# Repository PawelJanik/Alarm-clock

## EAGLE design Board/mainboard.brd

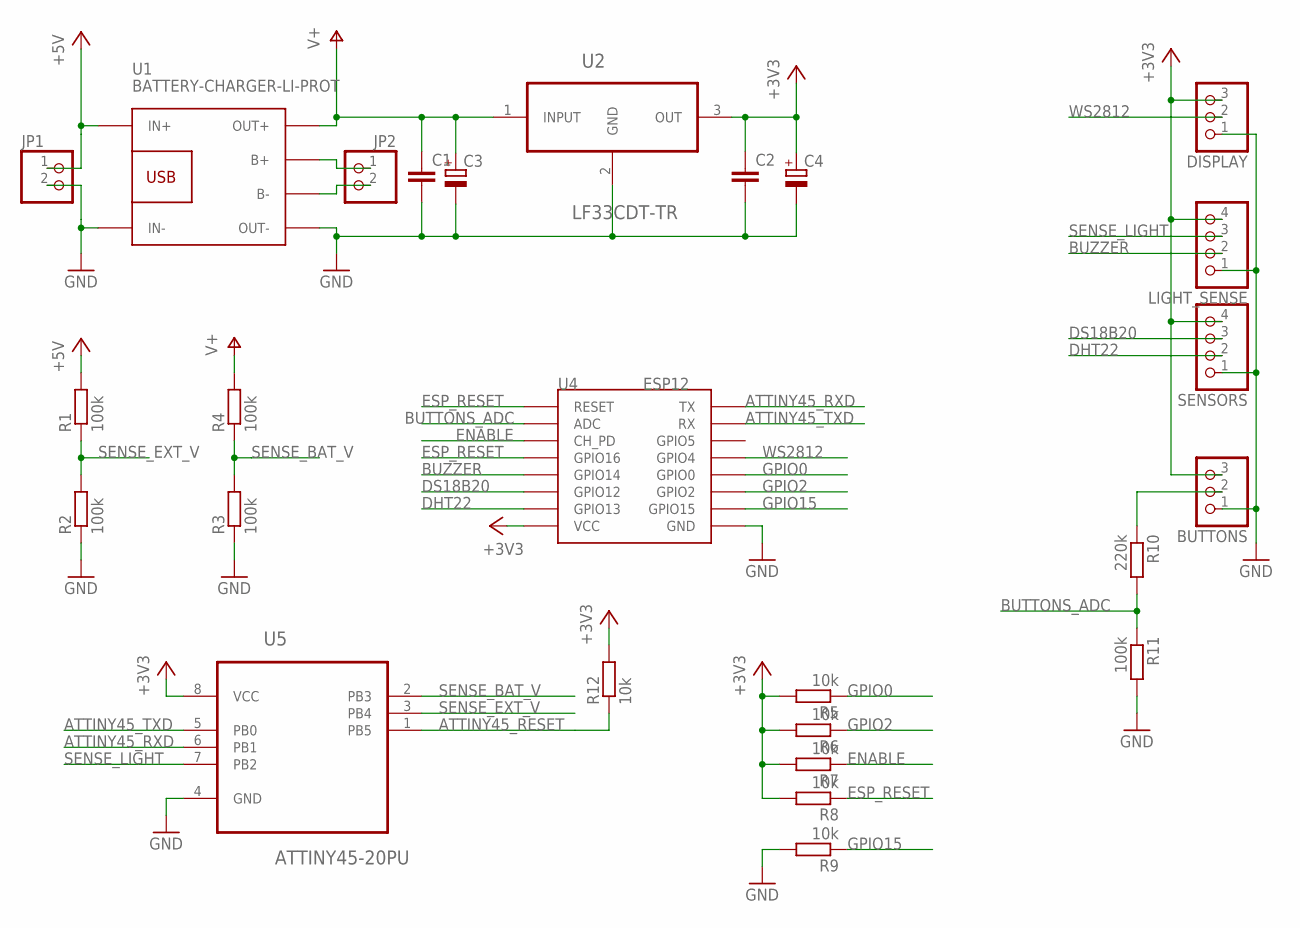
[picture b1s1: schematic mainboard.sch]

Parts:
BUTTONS: PINHD-1X3; 1X03
C1, C2: C-EUC1206; C1206
C3, C4: CPOL-EUE2-5; E2-5
DISPLAY: PINHD-1X3; 1X03
JP1, JP2: PINHD-1X2; 1X02
LIGHT_SENSE: PINHD-1X4; 1X04
R1, R2, R3, R4, R11: 100k; R1206
R5, R6, R7, R8, R9, R12: 10k; R1206
R10: 220k; R1206
SENSORS: PINHD-1X4; 1X04
U1: BATTERY-CHARGER-LI-PROT
U2: LF33CDT-TR; TO228P972X240-3N
U4: ESP12
U5: ATTINY45-20PU; DIP254P762X533-8

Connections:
+3V3: BUTTONS.3, C2.1, C4.+, DISPLAY.3, LIGHT_SENSE.4, R5.2, R6.2, R7.2, R8.2, R12.2, SENSORS.4, U2.3 (OUT), U4.VCC, U5.8 (VCC)
+5V: JP1.1, R1.2, U1.IN+
ATTINY45_RESET: R12.1, U5.1 (PB5)
ATTINY45_RXD: U4.TX, U5.6 (PB1)
ATTINY45_TXD: U4.RX, U5.5 (PB0)
BUTTONS_ADC: R10.2, R11.1, U4.ADC
BUZZER: LIGHT_SENSE.2, U4.GPIO14
DHT22: SENSORS.2, U4.GPIO13
DS18B20: SENSORS.3, U4.GPIO12
ENABLE: R7.1, U4.CH_PD
ESP_RESET: R8.1, U4.GPIO16, U4.RESET
GND: BUTTONS.1, C1.2, C2.2, C3.-, C4.-, DISPLAY.1, JP1.2, LIGHT_SENSE.1, R2.1, R3.1, R9.2, R11.2, SENSORS.1, U1.IN-, U1.OUT-, U2.2 (GND), U4.GND, U5.4 (GND)
GPIO0: R5.1, U4.GPIO0
GPIO2: R6.1, U4.GPIO2
GPIO15: R9.1, U4.GPIO15
unnamed: BUTTONS.2, R10.1
unnamed: JP2.1, U1.B+
unnamed: JP2.2, U1.B-
SENSE_BAT_V: R3.2, R4.1, U5.2 (PB3)
SENSE_EXT_V: R1.1, R2.2, U5.3 (PB4)
SENSE_LIGHT: LIGHT_SENSE.3, U5.7 (PB2)
V+: C1.1, C3.+, R4.2, U1.OUT+, U2.1 (INPUT)
WS2812: DISPLAY.2, U4.GPIO5 (GPIO4)

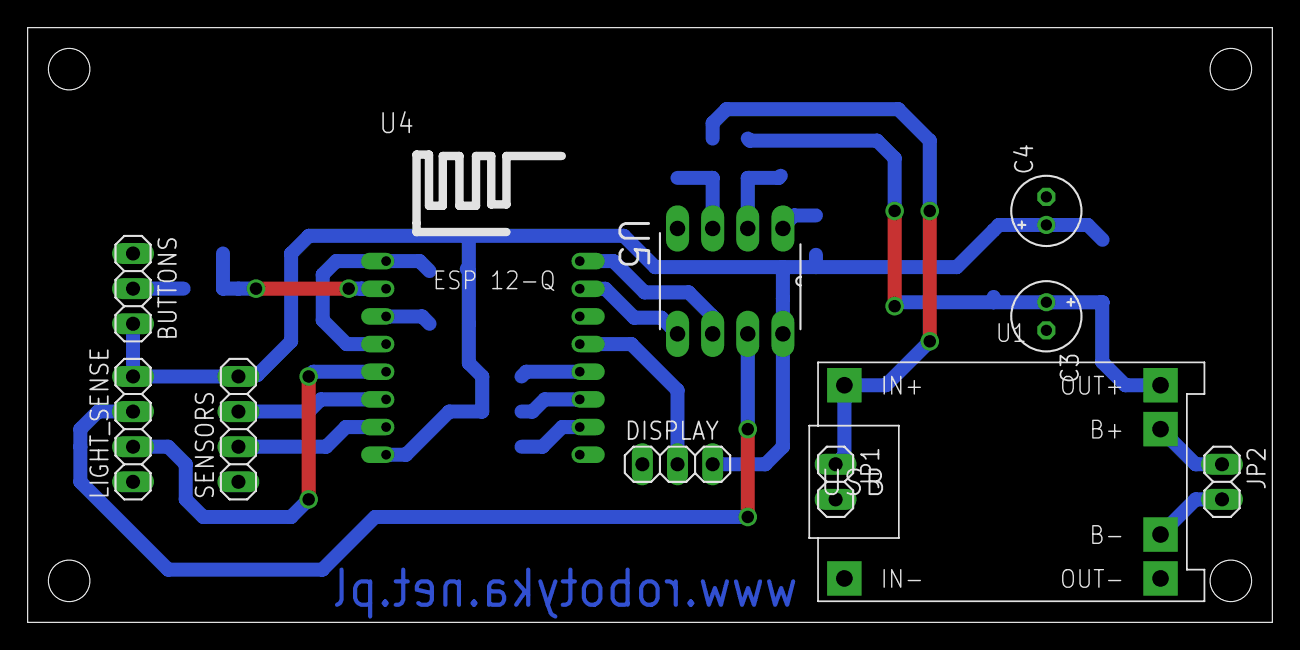
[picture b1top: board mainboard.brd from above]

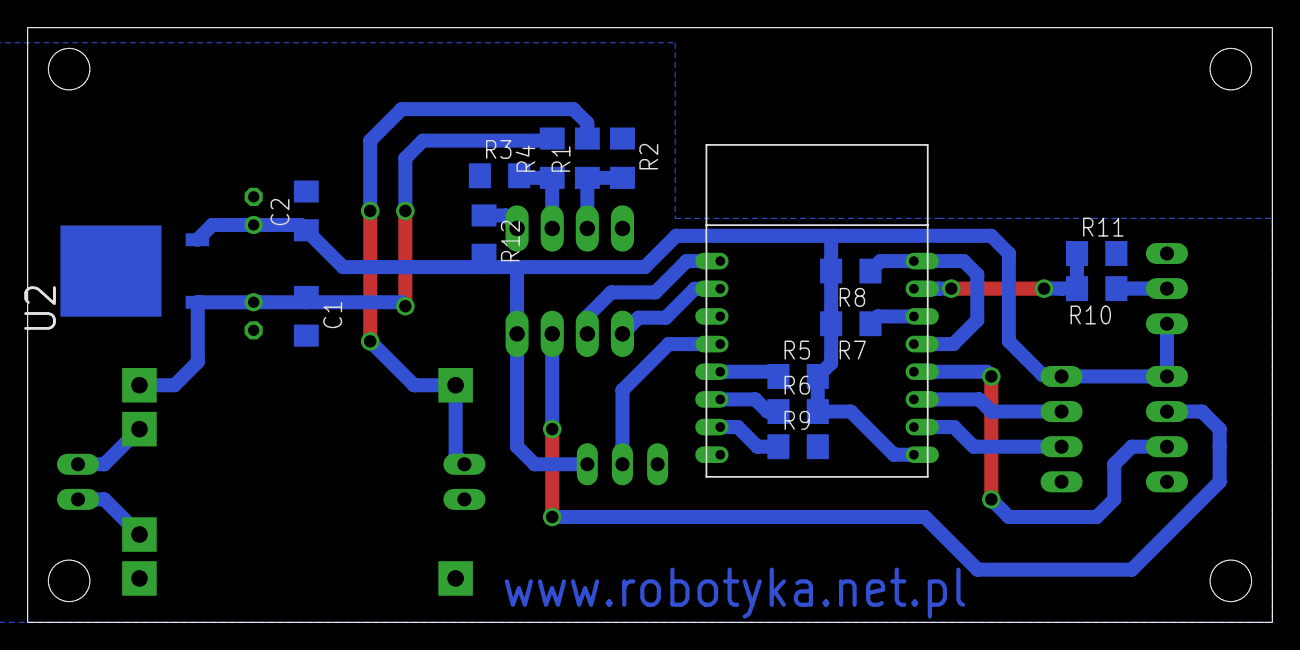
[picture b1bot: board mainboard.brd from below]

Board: 2 copper layers, 90.0 x 43.0 mm, 26 parts (15 on the bottom side), 23 nets.

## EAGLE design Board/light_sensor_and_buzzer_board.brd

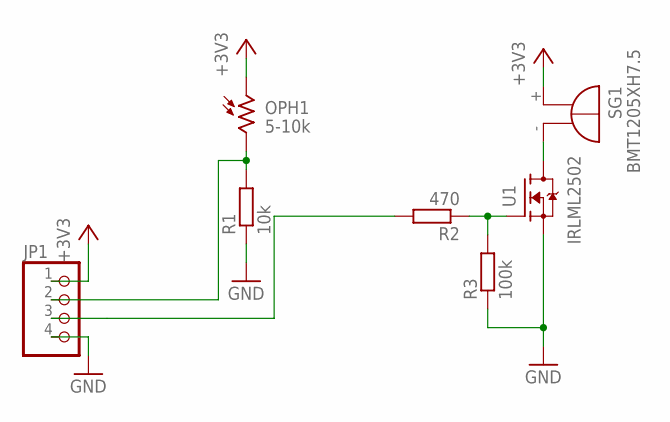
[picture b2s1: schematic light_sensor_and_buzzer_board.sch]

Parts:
JP1: PINHD-1X4; 1X04
OPH1: 5-10k; VT900
R1: 10k; R1206
R2: 470; R1206
R3: 100k; R1206
SG1: BMT1205XH7.5
U1: IRLML2502; SOT23

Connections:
+3V3: JP1.1, OPH1.1, SG1.+
GND: JP1.4, R1.1, R3.1, U1.2 (S)
unnamed: JP1.2, OPH1.2, R1.2
unnamed: SG1.-, U1.3 (D)
unnamed: R2.1, R3.2, U1.1 (G)
unnamed: JP1.3, R2.2

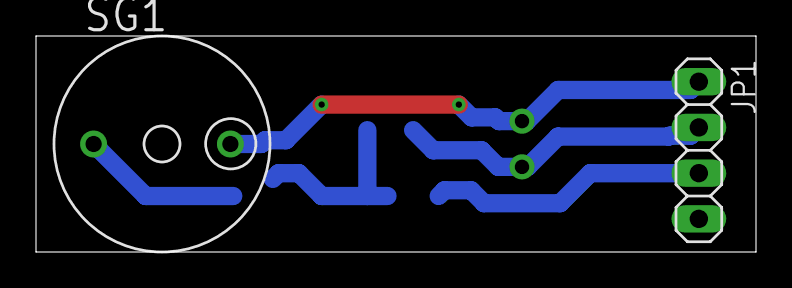
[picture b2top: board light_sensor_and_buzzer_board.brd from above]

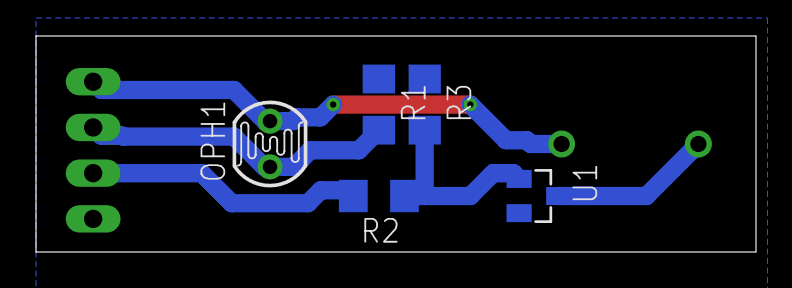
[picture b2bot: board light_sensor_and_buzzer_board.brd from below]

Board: 2 copper layers, 40.0 x 12.0 mm, 7 parts (5 on the bottom side), 6 nets.

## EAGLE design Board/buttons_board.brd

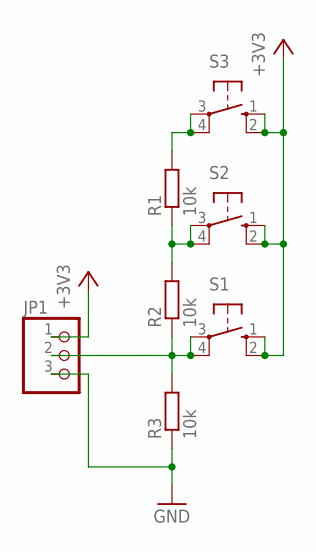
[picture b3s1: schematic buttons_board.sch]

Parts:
JP1: PINHD-1X3/90; 1X03/90
R1, R2, R3: 10k; R1206
S1, S2, S3: 10-XX; B3F-10XX

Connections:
+3V3: JP1.1, S1.1 (S), S1.2 (S1), S2.1 (S), S2.2 (S1), S3.1 (S), S3.2 (S1)
GND: JP1.3, R3.1
unnamed: JP1.2, R2.1, R3.2, S1.3, S1.4 (P1)
unnamed: R1.1, R2.2, S2.3, S2.4 (P1)
unnamed: R1.2, S3.3, S3.4 (P1)

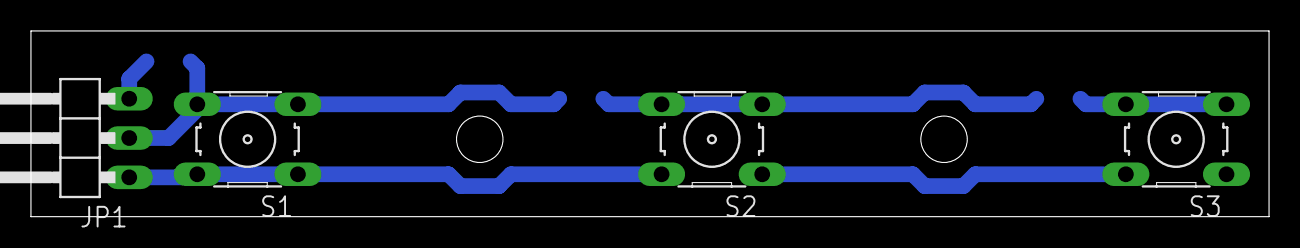
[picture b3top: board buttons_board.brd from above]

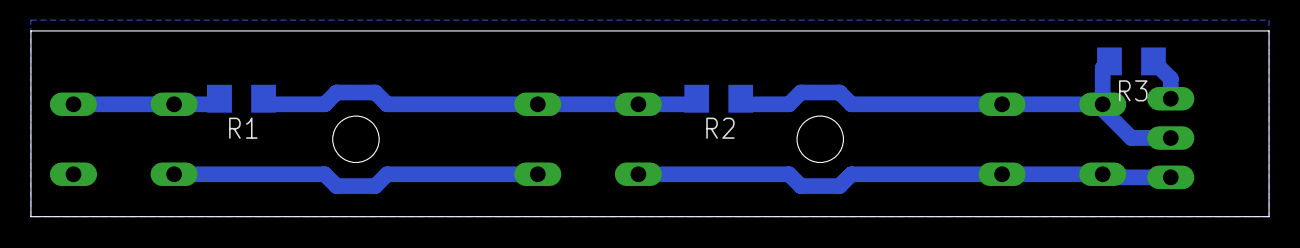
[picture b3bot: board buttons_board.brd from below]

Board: 2 copper layers, 80.0 x 12.0 mm, 7 parts (3 on the bottom side), 5 nets.

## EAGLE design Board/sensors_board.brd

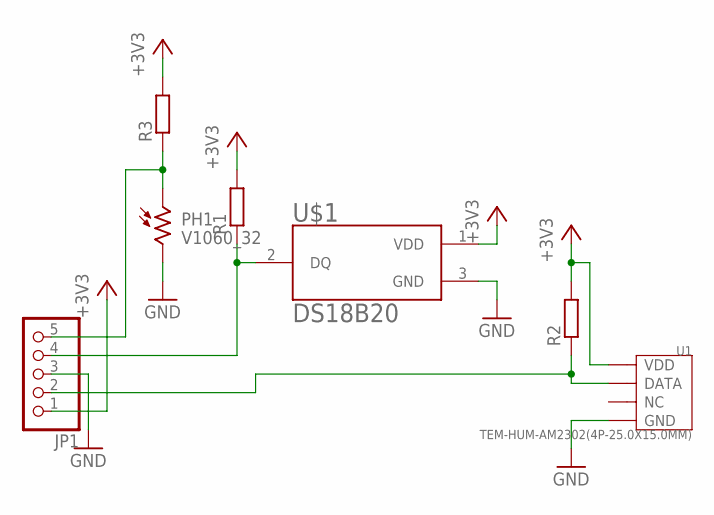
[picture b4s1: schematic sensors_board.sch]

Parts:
JP1: PINHD-1X5/90; 1X05/90
PH1: V1060_32; TO-5_V10
R1, R2, R3: R-EU_R1206; R1206
U1: TEM-HUM-AM2302(4P-25.0X15.0MM); SNR4-2.54-25.0X15.0X7.0MM
U$1: DS18B20; TO92-

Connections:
+3V3: JP1.1, R1.2, R2.2, R3.2, U1.P$1 (VDD), U$1.1 (VDD)
GND: JP1.3, PH1.2, U1.P$4 (GND), U$1.3 (GND)
unnamed: JP1.2, R2.1, U1.P$2 (DATA)
unnamed: JP1.4, R1.1, U$1.2 (DQ)
unnamed: JP1.5, PH1.1, R3.1

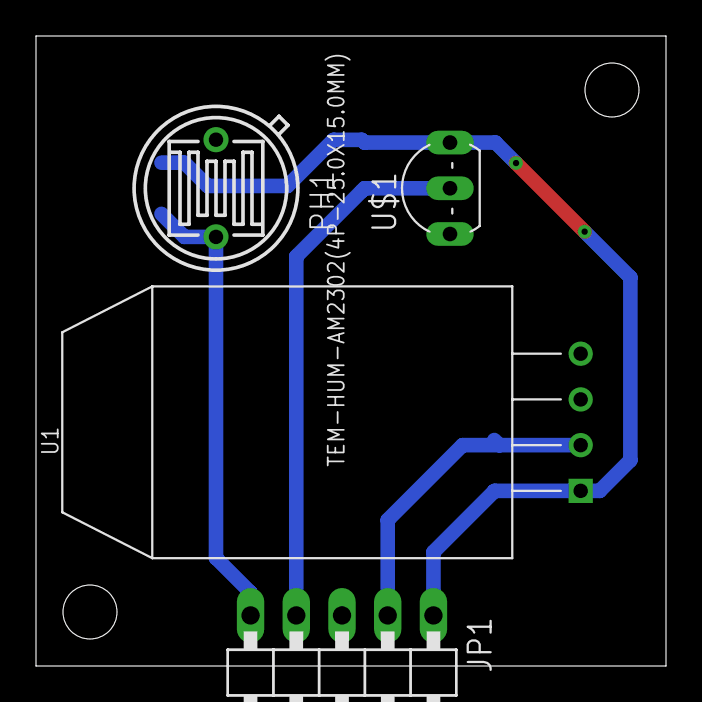
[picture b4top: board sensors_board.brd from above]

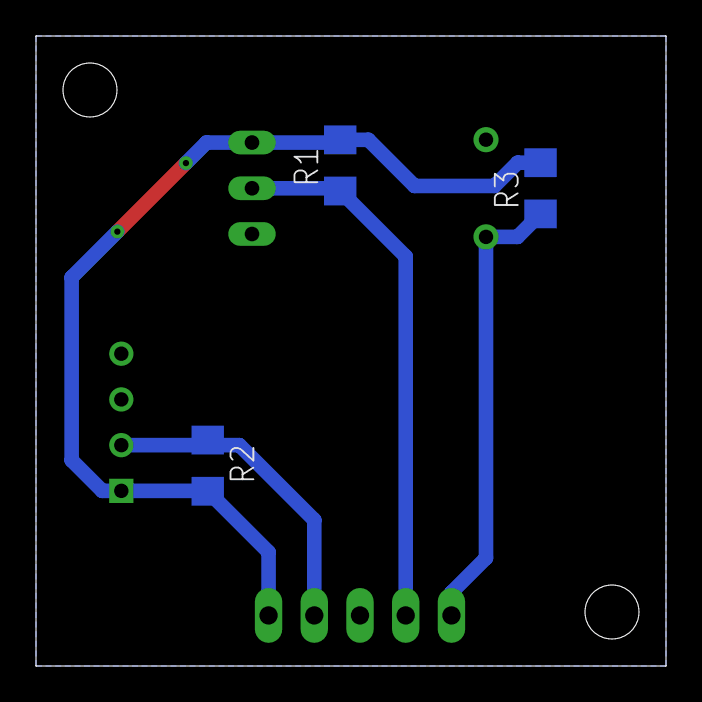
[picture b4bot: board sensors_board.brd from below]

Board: 2 copper layers, 35.0 x 35.0 mm, 7 parts (3 on the bottom side), 5 nets.

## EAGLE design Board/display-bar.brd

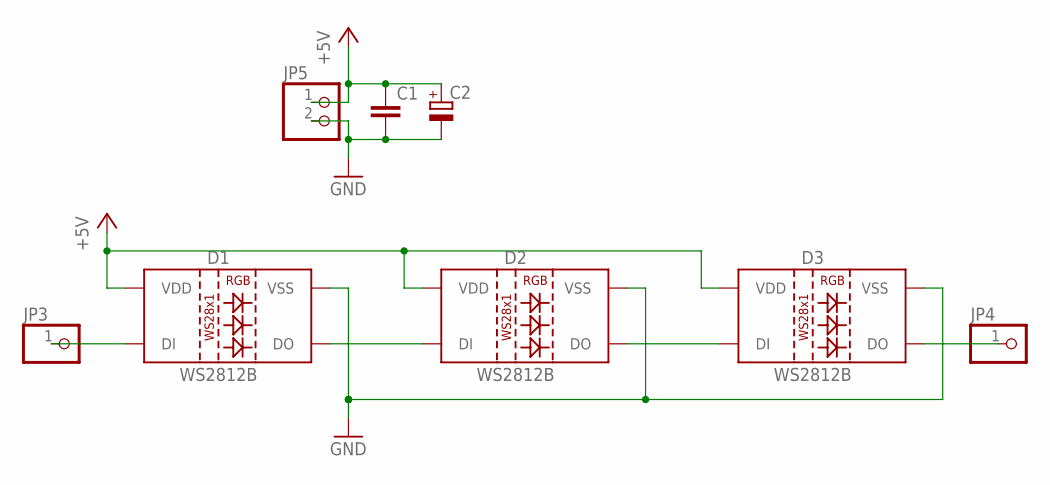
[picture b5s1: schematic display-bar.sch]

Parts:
C1: C-EUC1206; C1206
C2: CPOL-EUE2.5-6; E2,5-6
D1, D2, D3: WS2812B
JP3, JP4: PINHD-1X1; 1X01
JP5: PINHD-1X2; 1X02

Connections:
+5V: C1.1, C2.+, D1.1 (VDD), D2.1 (VDD), D3.1 (VDD), JP5.1
GND: C1.2, C2.-, D1.3 (VSS), D2.3 (VSS), D3.3 (VSS), JP5.2
unnamed: D3.2 (DO), JP4.1
unnamed: D2.2 (DO), D3.4 (DI)
unnamed: D1.2 (DO), D2.4 (DI)
unnamed: D1.4 (DI), JP3.1

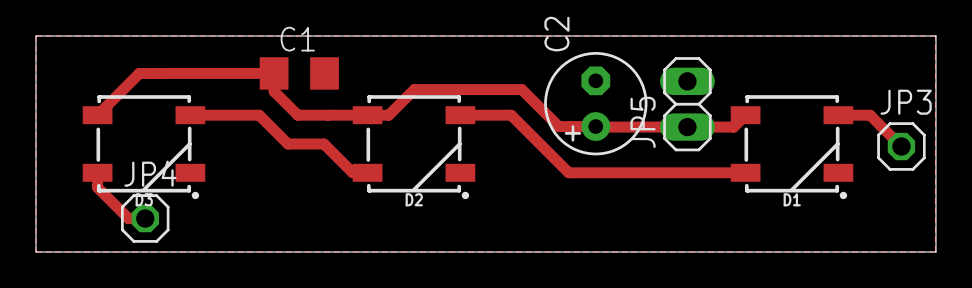
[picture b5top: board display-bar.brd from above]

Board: 2 copper layers, 50.0 x 12.0 mm, 8 parts (0 on the bottom side), 6 nets.

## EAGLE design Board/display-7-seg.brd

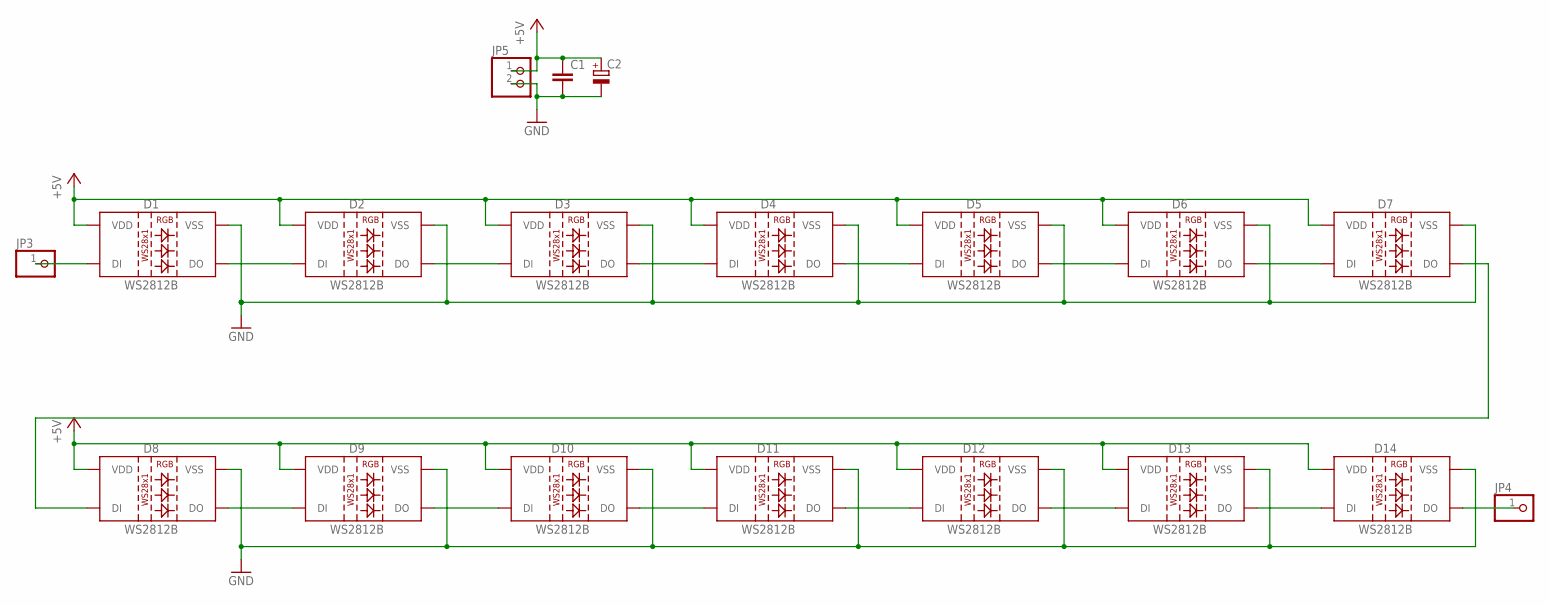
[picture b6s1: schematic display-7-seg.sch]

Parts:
C1: C-EUC1206; C1206
C2: CPOL-EUE2.5-6; E2,5-6
D1, D2, D3, D4, D5, D6, D7, D8, D9, D10, D11, D12, D13, D14: WS2812B
JP3, JP4: PINHD-1X1; 1X01
JP5: PINHD-1X2; 1X02

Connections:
+5V: C1.1, C2.+, D1.1 (VDD), D2.1 (VDD), D3.1 (VDD), D4.1 (VDD), D5.1 (VDD), D6.1 (VDD), D7.1 (VDD), D8.1 (VDD), D9.1 (VDD), D10.1 (VDD), D11.1 (VDD), D12.1 (VDD), D13.1 (VDD), D14.1 (VDD), JP5.1
GND: C1.2, C2.-, D1.3 (VSS), D2.3 (VSS), D3.3 (VSS), D4.3 (VSS), D5.3 (VSS), D6.3 (VSS), D7.3 (VSS), D8.3 (VSS), D9.3 (VSS), D10.3 (VSS), D11.3 (VSS), D12.3 (VSS), D13.3 (VSS), D14.3 (VSS), JP5.2
unnamed: D7.2 (DO), D8.4 (DI)
unnamed: D14.2 (DO), JP4.1
unnamed: D1.2 (DO), D2.4 (DI)
unnamed: D2.2 (DO), D3.4 (DI)
unnamed: D3.2 (DO), D4.4 (DI)
unnamed: D4.2 (DO), D5.4 (DI)
unnamed: D5.2 (DO), D6.4 (DI)
unnamed: D6.2 (DO), D7.4 (DI)
unnamed: D8.2 (DO), D9.4 (DI)
unnamed: D9.2 (DO), D10.4 (DI)
unnamed: D10.2 (DO), D11.4 (DI)
unnamed: D11.2 (DO), D12.4 (DI)
unnamed: D12.2 (DO), D13.4 (DI)
unnamed: D13.2 (DO), D14.4 (DI)
unnamed: D1.4 (DI), JP3.1

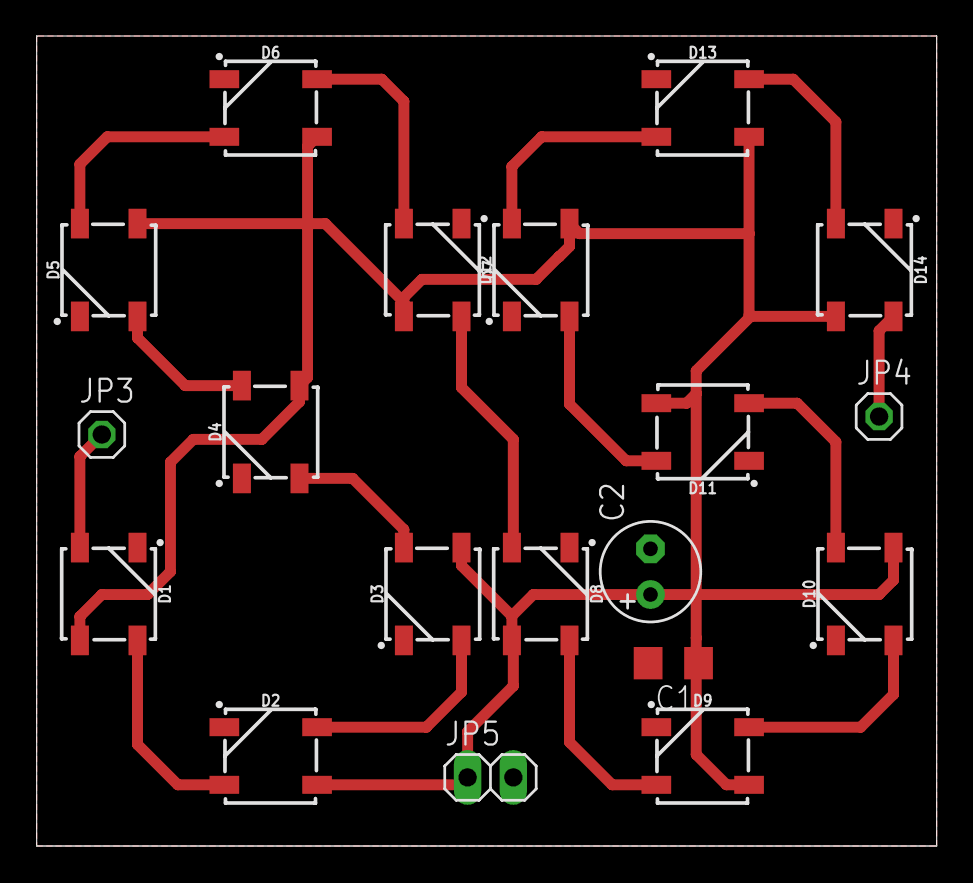
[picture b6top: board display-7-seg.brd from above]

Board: 2 copper layers, 50.0 x 45.0 mm, 19 parts (0 on the bottom side), 17 nets.

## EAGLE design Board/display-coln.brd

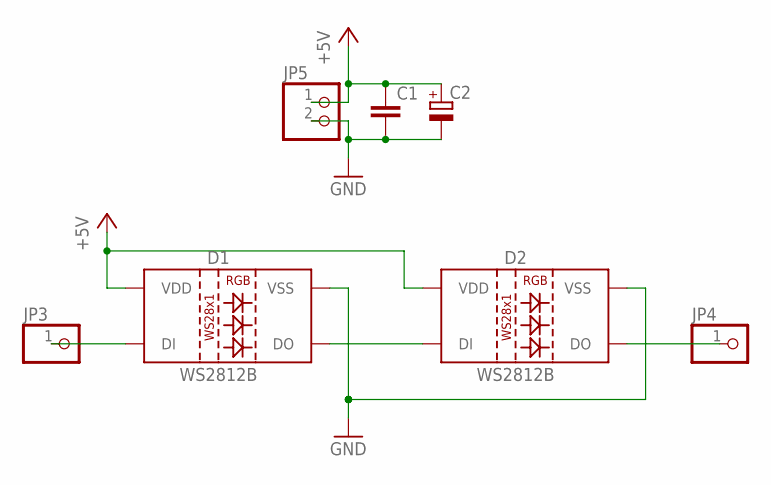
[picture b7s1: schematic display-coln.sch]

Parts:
C1: C-EUC1206; C1206
C2: CPOL-EUE2.5-6; E2,5-6
D1, D2: WS2812B
JP3, JP4: PINHD-1X1; 1X01
JP5: PINHD-1X2; 1X02

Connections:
+5V: C1.1, C2.+, D1.1 (VDD), D2.1 (VDD), JP5.1
GND: C1.2, C2.-, D1.3 (VSS), D2.3 (VSS), JP5.2
unnamed: D2.2 (DO), JP4.1
unnamed: D1.2 (DO), D2.4 (DI)
unnamed: D1.4 (DI), JP3.1

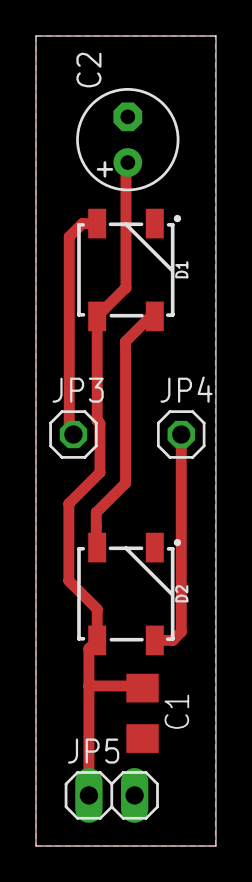
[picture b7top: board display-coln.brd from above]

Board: 2 copper layers, 10.0 x 45.0 mm, 7 parts (0 on the bottom side), 5 nets.

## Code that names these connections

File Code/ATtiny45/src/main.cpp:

#include <Arduino.h>
#include <avr/sleep.h>
#include "prescaler.h"

#define SENSE_EXT_V_PIN A2
#define SENSE_BAT_V_PIN A3
#define SENSE_LIGHT_PIN A1

#define ANALOG_RATIO 3.22	//----for 3.3V
//#define ANALOG_RATIO 4.88	//----for 5V

unsigned long timer200ms = 0;
unsigned long timer5s = 0;
unsigned long timer1m = 0;

int16_t lastLightValue = 0;
unsigned long lightTimer = 0;

void setup()
{
	setClockPrescaler(CLOCK_PRESCALER_8);	//-----------------------------------------------------------
	pinMode(3, OUTPUT);

	pinMode(SENSE_EXT_V_PIN, INPUT);
	pinMode(SENSE_BAT_V_PIN, INPUT);

	Serial.begin(9600);
}

void loop()
{
	if((millis() - timer200ms) > 200)
	{
		timer200ms = millis();

		int16_t lightValue = analogRead(SENSE_LIGHT_PIN);
		if(((lightValue - 10) > lastLightValue) || ((lightValue + 10) < lastLightValue))
		{
			Serial.print("-LIG:");
			Serial.println(lightValue);
			lastLightValue = lightValue;
		}
		else if((millis() - lightTimer) > 1000)
		{
			lightTimer = millis();

			Serial.print("-LIG:");
			Serial.println(lightValue);
			lastLightValue = lightValue;
		}
	}

	if((millis() - timer5s) > 1000*5)	//----------------------------to changed
	{
		timer5s = millis();

		Serial.print("-EXT:");
		Serial.println(analogRead(SENSE_EXT_V_PIN)*(double)ANALOG_RATIO/500);
	}

	if((millis() - timer1m) > 10000*60)
	{
		timer1m = millis();

		Serial.print("-BAT:");
		Serial.println(analogRead(SENSE_BAT_V_PIN)*(double)ANALOG_RATIO/500);
	}
}

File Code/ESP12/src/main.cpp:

#include "config.h"
#include "main.h"

#include <PubSubClient.h>
#include <ESP8266WiFi.h>
#include <ESP8266mDNS.h>
#include <WiFiUdp.h>
#include <ArduinoOTA.h>
#include <EEPROM.h>

#include <Adafruit_NeoPixel.h>

#include <TimeLib.h>
#include <NTPClient.h>

#include <Adafruit_Sensor.h>
#include <DHT.h>

#include <OneWire.h>
#include <DallasTemperature.h>

#include "setup.h"
#include "display.h"

#define WS2812_PIN 4
#define DHT_PIN 13
#define DS18B20_PIN 12
#define BUZZER_PIN 14
#define BUTTONS_PIN A0

#define DHTTYPE DHT22     // DHT 22 (AM2302)
#define pixelCount 33

unsigned long timer10ms = 0;
unsigned long timer1s = 0;
unsigned long timer10s = 0;
unsigned long timer1m = 0;

WiFiClient espClient;
PubSubClient client(espClient);

WiFiUDP ntpUDP;
NTPClient timeClient(ntpUDP, "europe.pool.ntp.org");

Adafruit_NeoPixel strip = Adafruit_NeoPixel(pixelCount, WS2812_PIN, NEO_GRB + NEO_KHZ800);
Display * display;

DHT dht(DHT_PIN, DHTTYPE);

OneWire oneWire(DS18B20_PIN);
DallasTemperature ds18b20(&oneWire);

ButtonState buttonsState[3];

time_t requestSync()
{
	timeClient.update();
	time_t timestamp = timeClient.getEpochTime();
	setTime(timestamp);

	return 0;
}

void reconnect()
{
	digitalWrite(1, LOW);

	//if (client.connect(controllerName, mqttLogin, mqttPasswd))
	if (client.connect(controllerName))
	{
		client.subscribe("home/controllers/3/restart");
		client.subscribe("home/controllers/3/sleep");

		client.subscribe("home/myRoom/alarmClock/dateTime/timestamp");
		client.subscribe("home/myRoom/alarmClock/dateTime/timeZone");
		client.subscribe("home/myRoom/alarmClock/dateTime/DST");

		client.subscribe("home/myRoom/alarmClock/brightness");
		client.subscribe("home/myRoom/alarmClock/displayColor");
		client.subscribe("home/myRoom/alarmClock/displayState");

		client.subscribe("home/myRoom/alarmClock/tempInColor");
		client.subscribe("home/myRoom/alarmClock/tempOutColor");

		client.subscribe("home/myRoom/alarmClock/buzzerState");

		digitalWrite(1, HIGH);
	}
}

void callback(char * topic, byte* payload, unsigned int length)
{
	if(strcmp(topic,"home/controllers/3/restart")==0)
	{
		if((char)payload[0] == 'r')
		{
			client.publish("home/controllers/3/condition", "reset");
			delay(500);

			ESP.restart();
		}
	}

	if(strcmp(topic,"home/controllers/3/sleep")==0)
	{
		if((char)payload[0] == 's')
		{
			client.publish("home/controllers/3/condition", "sleep");
			delay(500);

			ESP.deepSleep(5 * 1000000, WAKE_RF_DEFAULT);
			//-----------------------------------------------------------------------------------------
			delay(10);
		}
	}

	if(strcmp(topic,"home/myRoom/alarmClock/dateTime/timestamp")==0)
	{
		time_t timestamp = bytesToInt(payload,length);

		setTime(timestamp);
	}

	if(strcmp(topic,"home/myRoom/alarmClock/dateTime/timeZone")==0)
	{
		int8_t timeZone = bytesToInt(payload,length);

		timeClient.setTimeOffset((timeZone * 3600) + (EEPROM.read(EEPROM_DST) * 3600));
		requestSync();

		EEPROM.write(EEPROM_TIME_ZONE, timeZone);
		EEPROM.commit();
	}

	if(strcmp(topic,"home/myRoom/alarmClock/dateTime/DST")==0)
	{
		int8_t DST = bytesToInt(payload,length);

		if((DST == 0) || (DST == 1))
		{
			timeClient.setTimeOffset((EEPROM.read(EEPROM_TIME_ZONE) * 3600) + (DST * 3600));
			requestSync();

			EEPROM.write(EEPROM_DST, DST);
			EEPROM.commit();
		}
	}

	if(strcmp(topic,"home/myRoom/alarmClock/brightness")==0)
	{
		int value = bytesToInt(payload,length);

		display->setBrightness(value);
	}

	if(strcmp(topic,"home/myRoom/alarmClock/displayColor")==0)
	{
		uint32_t color = bytesToUint32(payload,length);
		display->setColor(color);
	}

	if(strcmp(topic,"home/myRoom/alarmClock/displayState")==0)
	{
		char state = payload[0];

		if(state == '0')
		{
			display->displayOff(false,true,false,false);
		}
		else if(state == '1')
		{
			display->displayOn();
		}
	}

	if(strcmp(topic,"home/myRoom/alarmClock/tempInColor")==0)
	{
		uint32_t color = bytesToUint32(payload,length);
		display->setTempInColor(color);
	}

	if(strcmp(topic,"home/myRoom/alarmClock/tempOutColor")==0)
	{
		uint32_t color = bytesToUint32(payload,length);
		display->setTempOutColor(color);
	}

	if(strcmp(topic,"home/myRoom/alarmClock/buzzerState")==0)
	{
		char state = payload[0];

		if(state == '0')
		{
			digitalWrite(BUZZER_PIN, LOW);
		}
		else if(state == '1')
		{
			digitalWrite(BUZZER_PIN, HIGH);
		}
	}
}

void setup()
{
	Serial.begin(9600);

	EEPROM.begin(256);

	WIFIsetup();
	OTAsetup();
	client.setServer(mqttIP, mqttPort);
	client.setCallback(callback);
	reconnect();

	timeClient.setTimeOffset((EEPROM.read(EEPROM_TIME_ZONE) * 3600) + (EEPROM.read(EEPROM_DST) * 3600));
	timeClient.begin();
	setSyncProvider(requestSync);
	setSyncInterval(60);	//------------------------------------------------------to changed on 60*60*24

	display = new Display(&strip);

	display->setColor(234534534);
	display->setAnimatedColon(true);

	dht.begin();
	ds18b20.begin();

	pinMode(BUZZER_PIN, OUTPUT);
	pinMode(BUTTONS_PIN, INPUT);
}

void loop()
{
	if (!client.connected())
	{
		reconnect();
	}
	else
	{
		client.loop();
		ArduinoOTA.handle();
	}

	if((millis() - timer10ms) > 5)
	{
		timer10ms = millis();

		readKey(buttonsState, &client);
	}

	if((millis() - timer1s) > 1000)
	{
		timer1s = millis();

		display->animation();

		display->setTime(hour(), minute());
		display->setAlarm(true);	//-----------------------------------------------------------------
	}

	if((millis() - timer10s) > 10000)
	{
		timer10s = millis();
		client.publish("home/controllers/3/condition", "ok");
	}

	if((millis() - timer1m) > 60000)
	{
		timer1m = millis();

		client.publish("home/sensors/temperature/7", String(dht.readTemperature()).c_str());
		client.publish("home/sensors/humidity/0", String(dht.readHumidity()).c_str());

		ds18b20.requestTemperatures();
		client.publish("home/sensors/temperature/8", String(ds18b20.getTempCByIndex(0)).c_str());
	}

	if (Serial.available() > 0)
	{
		String str = Serial.readStringUntil('\n');

		if(str.substring(1,4) == "BAT")
		{
			client.publish("home/controllers/3/batteryVoltage", str.substring(5,9).c_str());
		}
		else if(str.substring(1,4) == "EXT")
		{
			client.publish("home/controllers/3/externalPowerVoltage", str.substring(5,9).c_str());
		}
		else if(str.substring(1,4) == "LIG")
		{
			client.publish("home/sensors/light/1", str.substring(5,10).c_str());
		}
	}
}

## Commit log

2019-04-21 Display
    - display schematic and PCB
    - dxf for laser cutting of stainless elements
2019-04-21 Code
    - display support
    - clock
    - clock synchronization via NTP
2019-04-24 Add new files
    - motherboard scheme
    - ATtiny13 code

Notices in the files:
parts and their libraries:
diy-modules: Released under the Creative Commons Attribution 4.0 International License: http://creativecommons.org/licenses/by/4.0
